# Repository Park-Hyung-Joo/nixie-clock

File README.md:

# nixie-clock
The first project I designed PCB board. Now I see many newbie points in this project

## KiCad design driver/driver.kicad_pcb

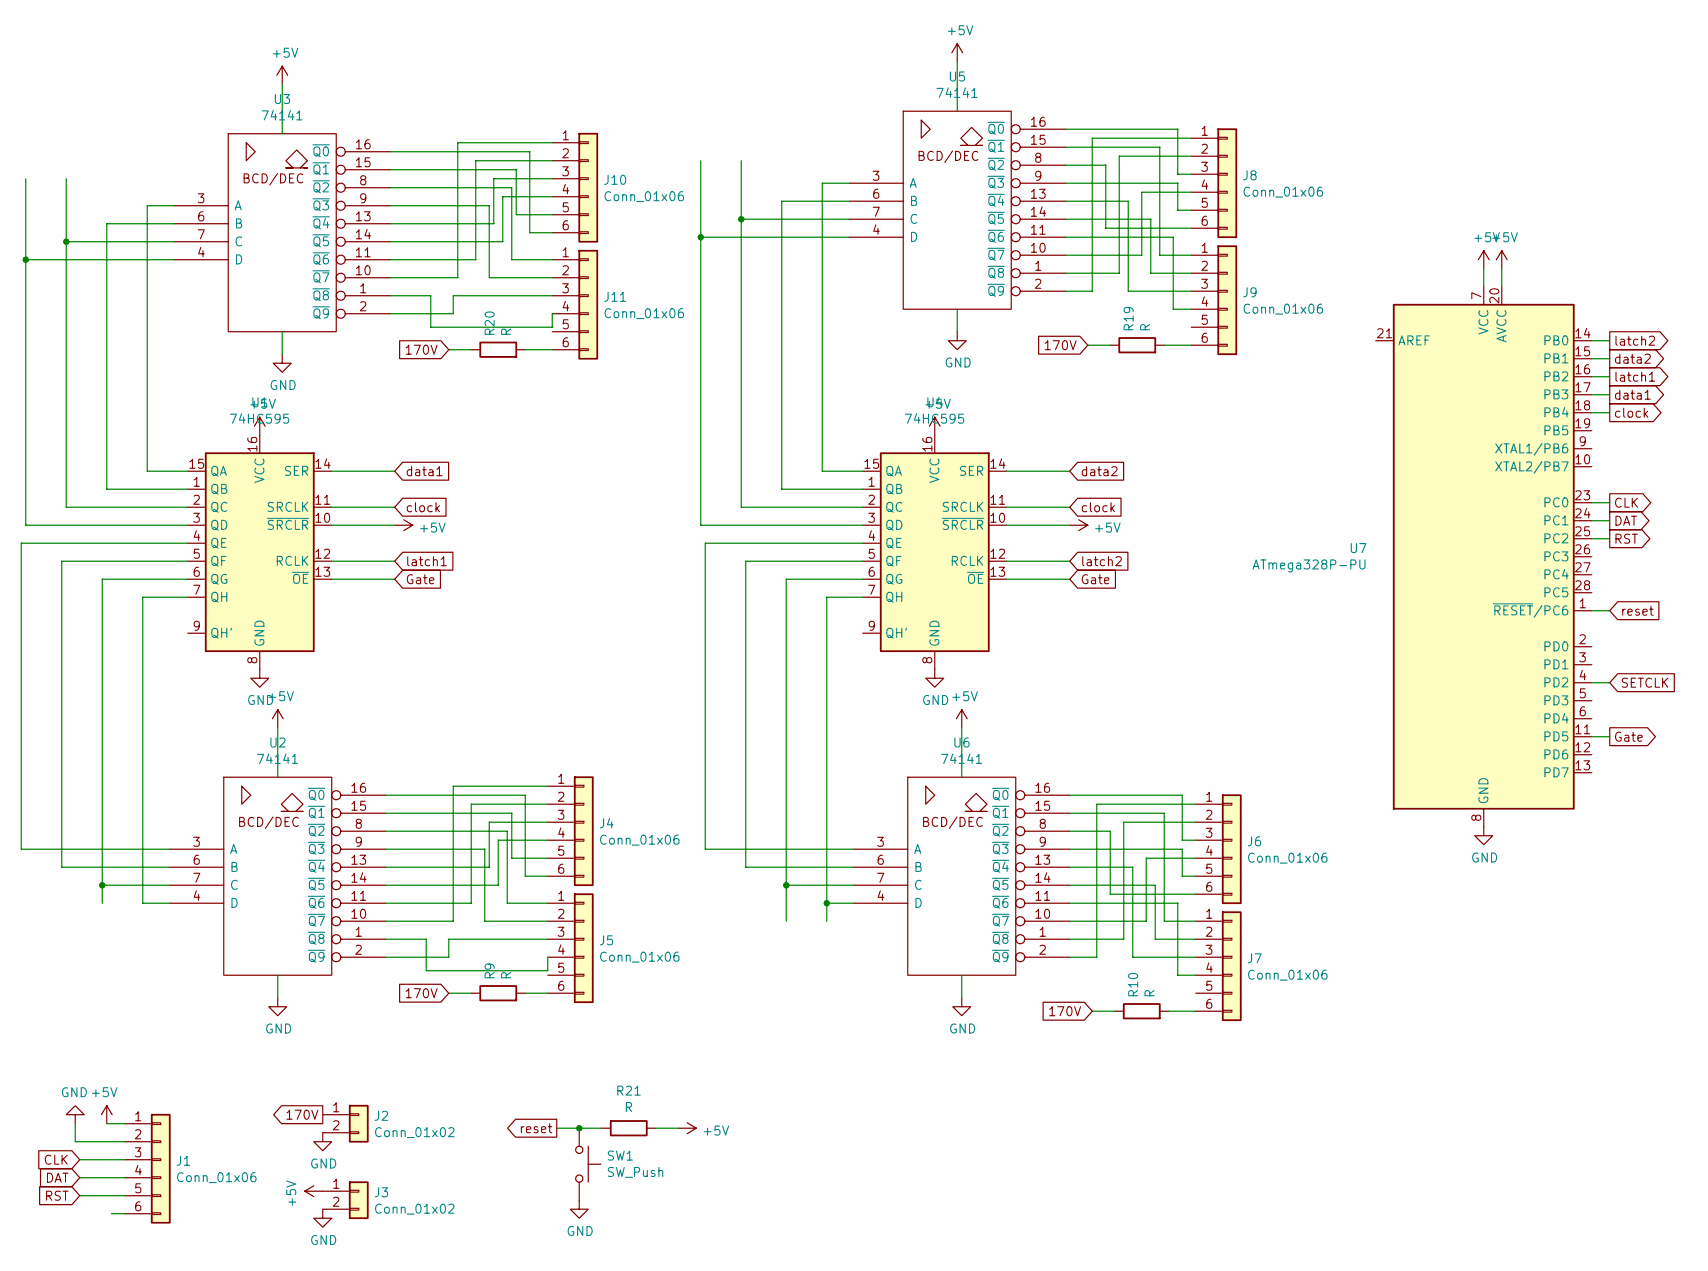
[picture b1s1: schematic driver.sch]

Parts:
J1: Conn_01x06; Molex_SPOX_5267-06A_1x06_P2.50mm_Vertical
J2, J3: Conn_01x02; Molex_SPOX_5267-02A_1x02_P2.50mm_Vertical
J4, J5, J6, J7, J10, J11: Conn_01x06; PinSocket_1x06_P2.54mm_Vertical
J8, J9: Conn_01x06; PinHeader_1x06_P2.54mm_Vertical
R9, R10, R19, R20, R21: R; R_Axial_DIN0309_L9.0mm_D3.2mm_P12.70mm_Horizontal
SW1: SW_Push; SW_PUSH_6mm_H5mm
U1, U4: 74HC595; DIP-16_W7.62mm_Socket
U2, U3, U5, U6: 74141; DIP-16_W7.62mm_Socket
U7: ATmega328P-PU; DIP-28_W7.62mm_Socket

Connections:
170V: J2.1, R9.1, R10.1, R19.1, R20.1
+5V: J1.1, J3.1, R21.1, U1.10 (~SRCLR), U1.16 (VCC), U2.5 (VCC), U3.5 (VCC), U4.10 (~SRCLR), U4.16 (VCC), U5.5 (VCC), U6.5 (VCC), U7.7 (VCC), U7.20 (AVCC)
CLK: J1.3, U7.23 (PC0)
DAT: J1.4, U7.24 (PC1)
GND: J1.2, J2.2, J3.2, SW1.2, U1.8 (GND), U2.12 (GND), U3.12 (GND), U4.8 (GND), U5.12 (GND), U6.12 (GND), U7.8 (GND), U7.22 (GND)
Gate: U1.13 (~OE), U4.13 (~OE), U7.11 (PD5)
unnamed: J4.1, U2.10 (~Q7)
unnamed: J4.2, U2.11 (~Q6)
unnamed: J4.3, U2.13 (~Q4)
unnamed: J4.4, U2.14 (~Q5)
unnamed: J4.5, U2.15 (~Q1)
unnamed: J4.6, U2.16 (~Q0)
unnamed: J5.1, U2.8 (~Q2)
unnamed: J5.2, U2.9 (~Q3)
unnamed: J5.3, U2.2 (~Q9)
unnamed: J5.4, U2.1 (~Q8)
unnamed: J5.6, R9.2
unnamed: J6.1, U6.2 (~Q9)
unnamed: J6.2, U6.1 (~Q8)
unnamed: J6.3, U6.16 (~Q0)
unnamed: J6.4, U6.10 (~Q7)
unnamed: J6.5, U6.9 (~Q3)
unnamed: J6.6, U6.8 (~Q2)
unnamed: J7.1, U6.15 (~Q1)
unnamed: J7.2, U6.14 (~Q5)
unnamed: J7.3, U6.13 (~Q4)
unnamed: J7.4, U6.11 (~Q6)
unnamed: J7.6, R10.2
unnamed: J8.1, U5.2 (~Q9)
unnamed: J8.2, U5.1 (~Q8)
unnamed: J8.3, U5.16 (~Q0)
unnamed: J8.4, U5.10 (~Q7)
unnamed: J8.5, U5.9 (~Q3)
unnamed: J8.6, U5.8 (~Q2)
unnamed: J9.1, U5.15 (~Q1)
unnamed: J9.2, U5.14 (~Q5)
unnamed: J9.3, U5.13 (~Q4)
unnamed: J9.4, U5.11 (~Q6)
unnamed: J9.6, R19.2
unnamed: J10.1, U3.10 (~Q7)
unnamed: J10.2, U3.11 (~Q6)
unnamed: J10.3, U3.13 (~Q4)
unnamed: J10.4, U3.14 (~Q5)
unnamed: J10.5, U3.15 (~Q1)
unnamed: J10.6, U3.16 (~Q0)
unnamed: J11.1, U3.8 (~Q2)
unnamed: J11.2, U3.9 (~Q3)
unnamed: J11.3, U3.2 (~Q9)
unnamed: J11.4, U3.1 (~Q8)
unnamed: J11.6, R20.2
unnamed: U1.1 (QB), U3.6 (B)
unnamed: U1.2 (QC), U3.7 (C)
unnamed: U1.3 (QD), U3.4 (D)
unnamed: U1.4 (QE), U2.3 (A)
unnamed: U1.5 (QF), U2.6 (B)
unnamed: U1.6 (QG), U2.7 (C)
unnamed: U1.7 (QH), U2.4 (D)
unnamed: U1.15 (QA), U3.3 (A)
unnamed: U4.1 (QB), U5.6 (B)
unnamed: U4.2 (QC), U5.7 (C)
unnamed: U4.3 (QD), U5.4 (D)
unnamed: U4.4 (QE), U6.3 (A)
unnamed: U4.5 (QF), U6.6 (B)
unnamed: U4.6 (QG), U6.7 (C)
unnamed: U4.7 (QH), U6.4 (D)
unnamed: U4.15 (QA), U5.3 (A)
RST: J1.5, U7.25 (PC2)
SETCLK: U7.4 (PD2)
clock: U1.11 (SRCLK), U4.11 (SRCLK), U7.18 (PB4)
data1: U1.14 (SER), U7.17 (PB3)
data2: U4.14 (SER), U7.15 (PB1)
latch1: U1.12 (RCLK), U7.16 (PB2)
latch2: U4.12 (RCLK), U7.14 (PB0)
reset: R21.2, SW1.1, U7.1 (~RESET~/PC6)

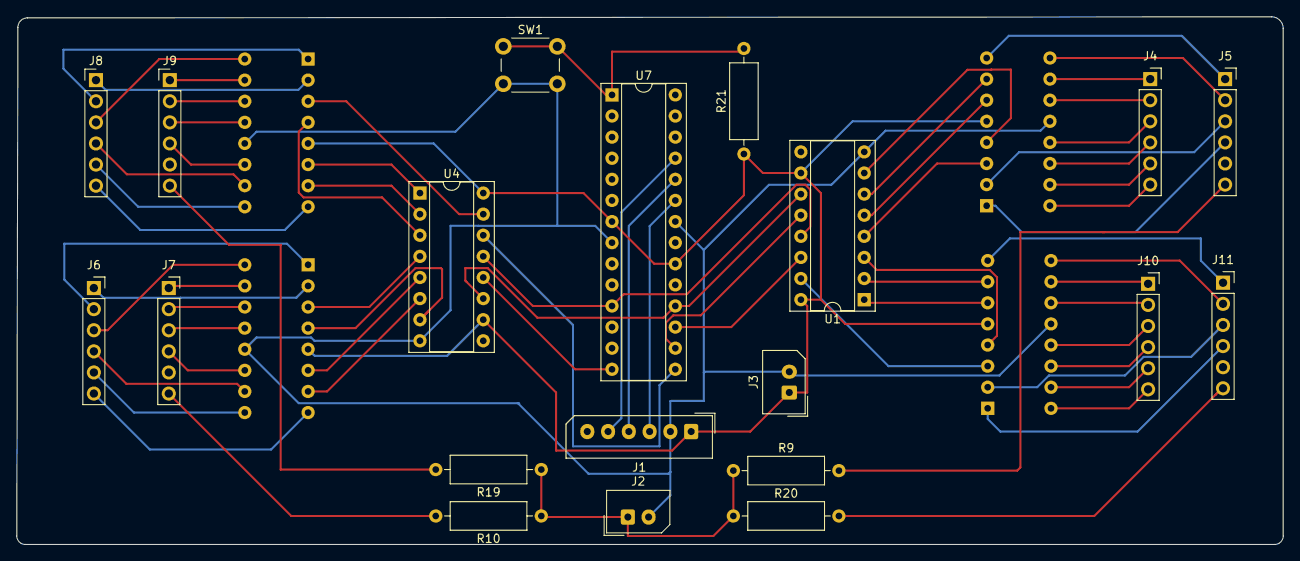
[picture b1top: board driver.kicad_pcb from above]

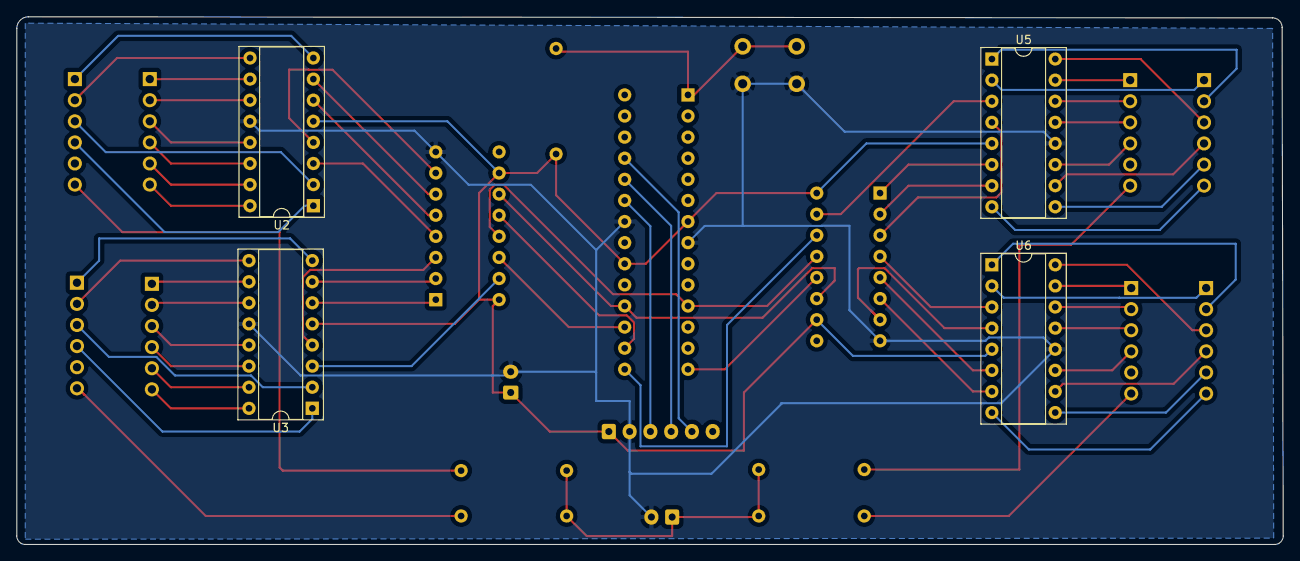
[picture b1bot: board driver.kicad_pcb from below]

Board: 2 copper layers, 152.4 x 63.5 mm, 24 parts (4 on the bottom side), 73 nets.

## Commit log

2021-08-22 add files
